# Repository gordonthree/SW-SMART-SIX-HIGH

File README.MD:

# Smart Six-way High Side Switch Node
Compact power management board intended to control six high-side DC loads. The node provides current monitoring of each load, and the board total. Temperature and supply voltage are also monitored. This node works with other CAN-CTL modules using the robust CAN bus interface.

<IMG src="https://github.com/gordonthree/SW-SMART-SIX-HIGH/blob/main/SW-SMART-SIX-HIGH.png?raw=true" width=480>

* STM32G071 microcontroller with 64 pins and 256k flash
* Six Infineon BTS7002 Profet Smart Switches for high side loads; firmware limited to 15 amps each
* Allegro ACS712 on board to monitor total board current; firmware limited to 30 amps
* Microchip MCP2562 isolated CAN bus transceiver
* Microchip MCP9701 board mount temperature sensor
* Voltage divider to monitor supply voltage
* Each switch provides current monitoring and diagnostics
* Screw terminal block for CAN bus connection
* Screw terminal block for power-out, up to 12 AWG
* Heavy duty screw terminals for power in, up to 6 AWG cable
* Headers for SWD programming and USART2 serial port

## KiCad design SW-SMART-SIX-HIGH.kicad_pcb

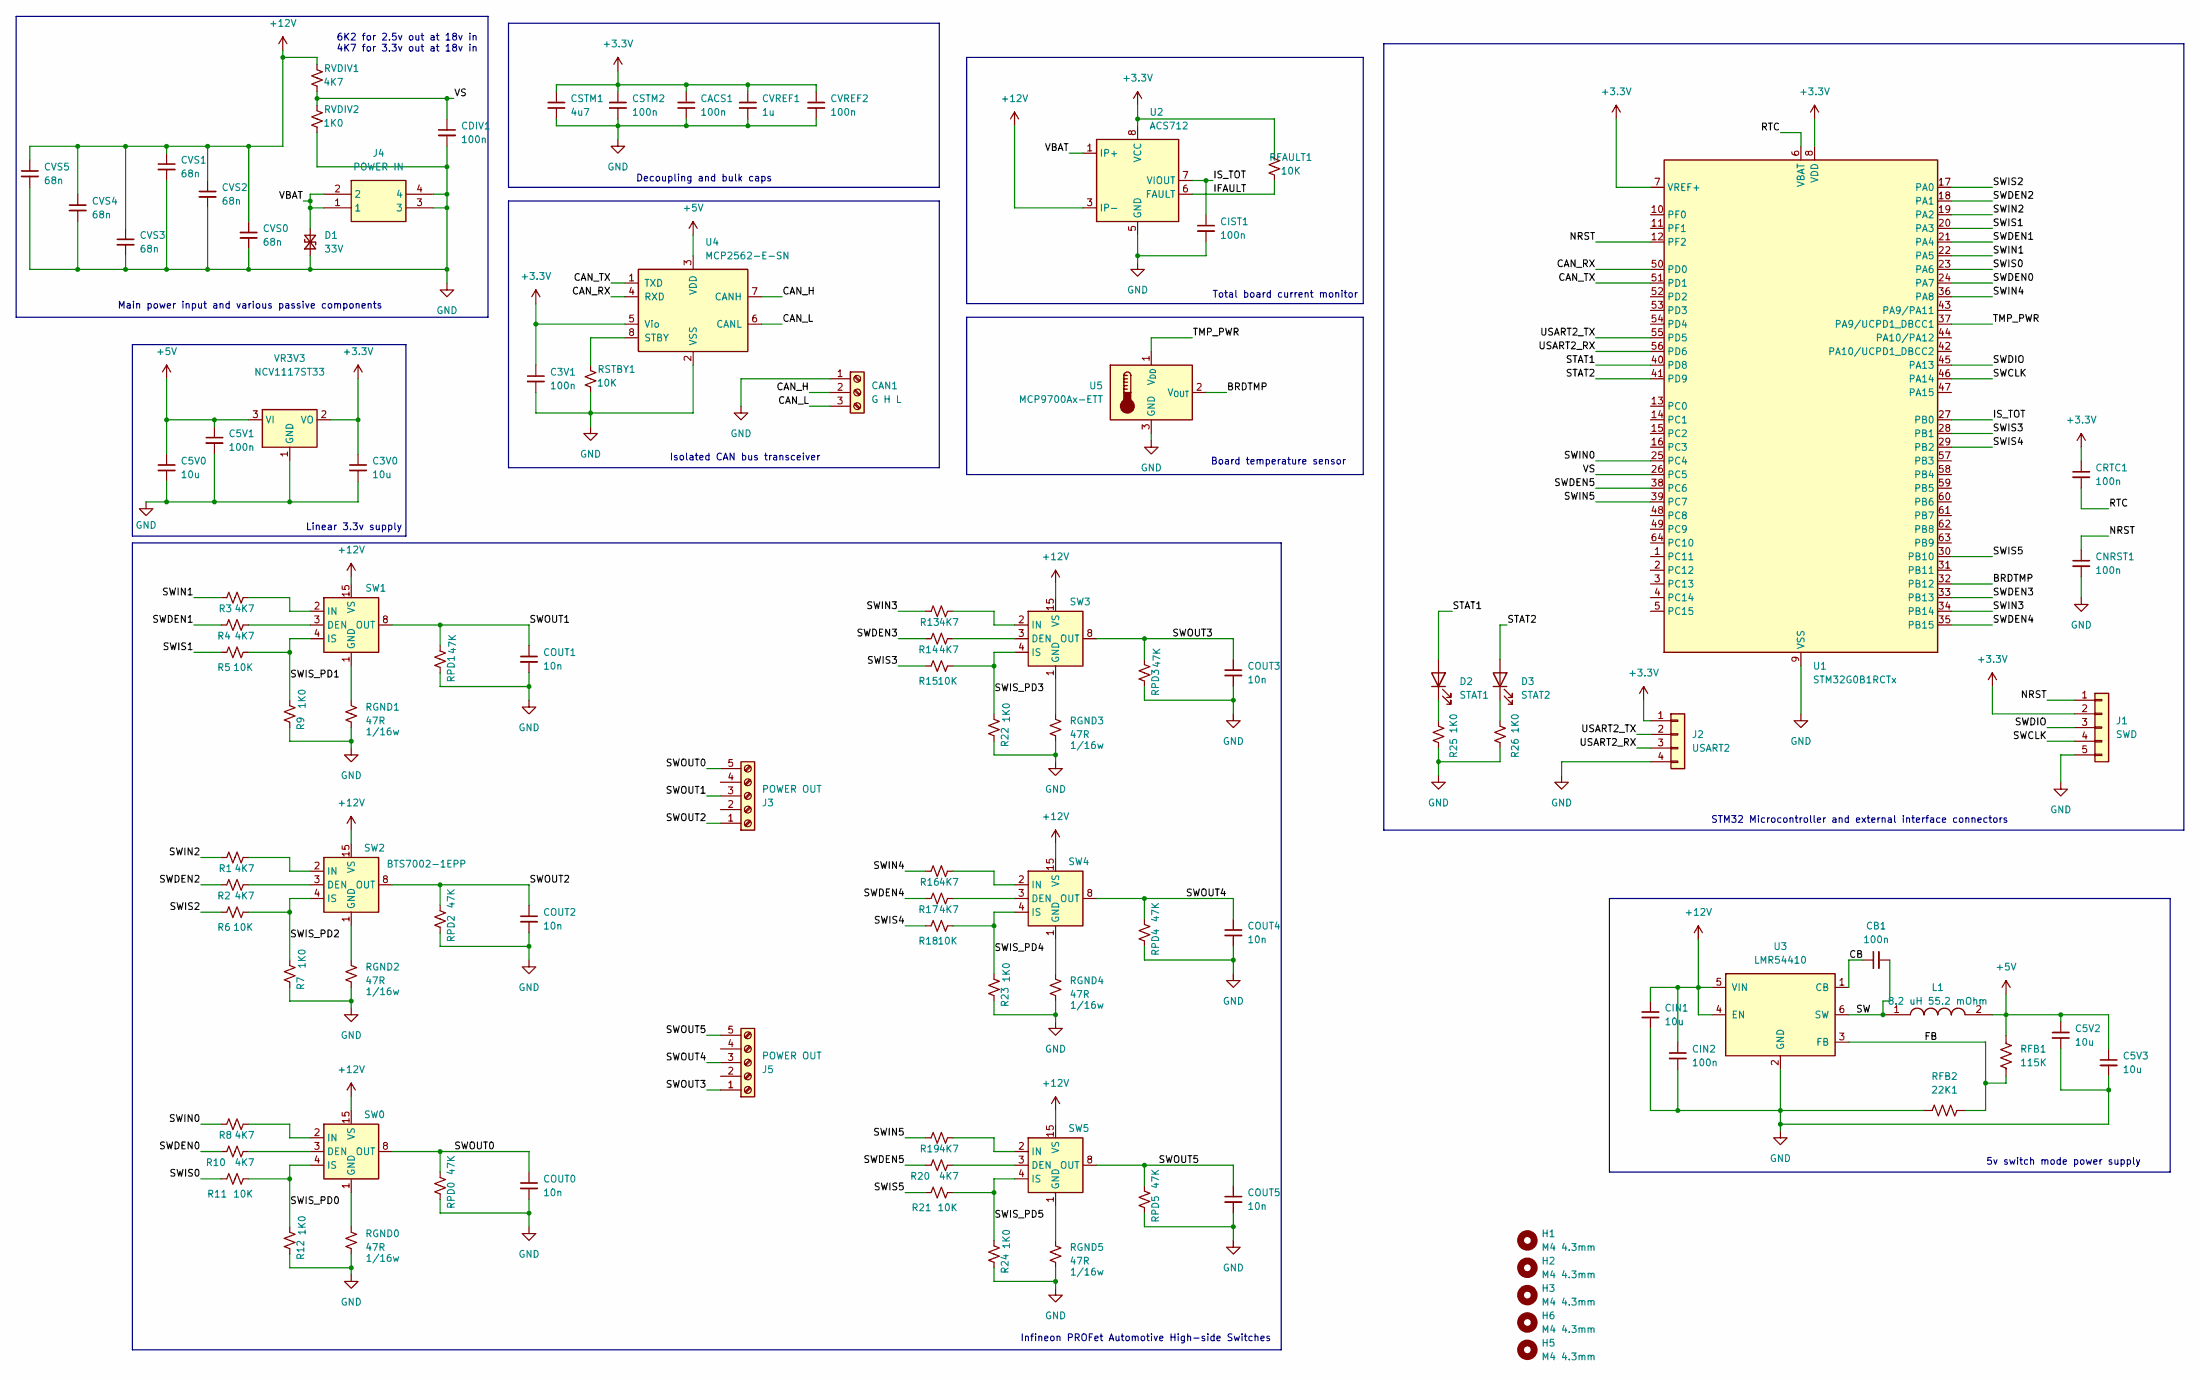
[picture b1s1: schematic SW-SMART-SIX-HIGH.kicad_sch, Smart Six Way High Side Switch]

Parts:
C3V0, C5V0, C5V2, C5V3: 10u; C_0805_2012Metric_Pad1.18x1.45mm_HandSolder
C3V1, C5V1: 100n; C_0603_1608Metric_Pad1.08x0.95mm_HandSolder
CACS1: 100n; C_0603_1608Metric_Pad1.08x0.95mm_HandSolder
CAN1: G H L; TerminalBlock_Phoenix_MPT-0,5-3-2.54_1x03_P2.54mm_Horizontal
CB1: 100n; C_0603_1608Metric_Pad1.08x0.95mm_HandSolder
CDIV1: 100n; C_0603_1608Metric_Pad1.08x0.95mm_HandSolder
CIN1: 10u; C_1210_3225Metric_Pad1.33x2.70mm_HandSolder
CIN2: 100n; C_0603_1608Metric_Pad1.08x0.95mm_HandSolder
CIST1: 100n; C_0603_1608Metric_Pad1.08x0.95mm_HandSolder
CNRST1: 100n; C_0603_1608Metric_Pad1.08x0.95mm_HandSolder
COUT0, COUT1, COUT2, COUT3, COUT4, COUT5: 10n; C_0603_1608Metric_Pad1.08x0.95mm_HandSolder
CRTC1: 100n; C_0603_1608Metric_Pad1.08x0.95mm_HandSolder
CSTM1: 4u7; C_0805_2012Metric_Pad1.18x1.45mm_HandSolder
CSTM2: 100n; C_0603_1608Metric_Pad1.08x0.95mm_HandSolder
CVREF1: 1u; C_0805_2012Metric_Pad1.18x1.45mm_HandSolder
CVREF2: 100n; C_0603_1608Metric_Pad1.08x0.95mm_HandSolder
CVS0, CVS1, CVS2, CVS3, CVS4, CVS5: 68n; C_0603_1608Metric_Pad1.08x0.95mm_HandSolder
D1: 33V; D_SMA_Handsoldering
D2: STAT1; LED_0805_2012Metric_Pad1.15x1.40mm_HandSolder
D3: STAT2; LED_0805_2012Metric_Pad1.15x1.40mm_HandSolder
H1, H2, H3, H5, H6: M4 4.3mm; MountingHole_4.3mm_M4
J1: SWD; PinHeader_1x05_P2.54mm_Vertical
J2: USART2; PinHeader_1x04_P2.54mm_Vertical
J3, J5: POWER OUT; TerminalBlock_Phoenix_MKDS-3-5-5.08_1x05_P5.08mm_Horizontal
J4: POWER IN; VP0265840000G; Mouser Part Number 649-VP02658400J0G
L1: 8.2 uH 55.2 mOhm; SRP5030HMT-8R2M; Mouser Part Number SRP5030HMT-8R2M
R1, R2, R3, R4, R8, R10, R13, R14, R16, R17, R19, R20: 4K7; R_0603_1608Metric_Pad0.98x0.95mm_HandSolder
R5, R6, R11, R15, R18, R21: 10K; R_0603_1608Metric_Pad0.98x0.95mm_HandSolder
R7, R9, R12, R22, R23, R24, R25, R26: 1K0; R_0603_1608Metric_Pad0.98x0.95mm_HandSolder
RFAULT1: 10K; R_0603_1608Metric_Pad0.98x0.95mm_HandSolder
RFB1: 115K; R_0603_1608Metric_Pad0.98x0.95mm_HandSolder
RFB2: 22K1; R_0603_1608Metric_Pad0.98x0.95mm_HandSolder
RGND0, RGND1, RGND2, RGND3, RGND4, RGND5: 47R; R_0603_1608Metric_Pad0.98x0.95mm_HandSolder
RPD0, RPD1, RPD2, RPD3, RPD4, RPD5: 47K; R_0603_1608Metric_Pad0.98x0.95mm_HandSolder
RSTBY1: 10K; R_0603_1608Metric_Pad0.98x0.95mm_HandSolder
RVDIV1: 4K7; R_0603_1608Metric_Pad0.98x0.95mm_HandSolder
RVDIV2: 1K0; R_0603_1608Metric_Pad0.98x0.95mm_HandSolder
SW0, SW1, SW2, SW3, SW4, SW5: BTS7002-1EPP; SOP65P600X115-15N
U1: STM32G0B1RCTx; LQFP-64_10x10mm_P0.5mm
U2: ACS712; SOIC-8_3.9x4.9mm_P1.27mm; Part Number ACS71240LLCBTR-050B3
U3: LMR54410; SOT-23-6
U4: MCP2562-E-SN; SOIC-8_3.9x4.9mm_P1.27mm
U5: MCP9700Ax-ETT; SOT-23
VR3V3: NCV1117ST33; SOT-223-3_TabPin2

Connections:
+3.3V: C3V0.1, C3V1.1, CACS1.1, CRTC1.1, CSTM1.1, CSTM2.1, CVREF1.1, CVREF2.1, J1.2, J2.1, RFAULT1.2, U1.7 (VREF+), U1.8 (VDD), U2.8 (VCC), U4.5 (Vio), VR3V3.2 (VO); also elsewhere on the board
+5V: C5V0.1, C5V1.1, C5V2.1, C5V3.1, L1.2, RFB1.1, U4.3 (VDD), VR3V3.3 (VI)
+12V: CIN1.1, CIN2.1, CVS0.1, CVS1.1, CVS2.1, CVS3.1, CVS4.1, CVS5.1, RVDIV1.2, SW0.15 (VS), SW1.15 (VS), SW2.15 (VS), SW3.15 (VS), SW4.15 (VS), SW5.15 (VS), U2.3 (IP-), U2.4 (IP-), U3.4 (EN), U3.5 (VIN)
/BRDTMP: U1.32 (PB12), U5.2 (V_{OUT})
/CAN_H: CAN1.2, U4.7 (CANH)
/CAN_L: CAN1.3, U4.6 (CANL)
/CAN_RX: U1.50 (PD0), U4.4 (RXD)
/CAN_TX: U1.51 (PD1), U4.1 (TXD)
/CB: CB1.1, U3.1 (CB)
/FB: RFB1.2, RFB2.2, U3.3 (FB)
/IFAULT: RFAULT1.1, U2.6 (FAULT)
/IS_TOT: CIST1.1, U1.27 (PB0), U2.7 (VIOUT)
/NRST: CNRST1.1, J1.1, U1.12 (PF2)
/OSC: U1.10 (PF0); also elsewhere on the board
/RTC: CRTC1.2, U1.6 (VBAT)
/STAT1: D2.2 (A), U1.40 (PD8)
/STAT2: D3.2 (A), U1.41 (PD9)
/SW: CB1.2, L1.1, U3.6 (SW)
/SWCLK: J1.4, U1.46 (PA14)
/SWDEN0: R10.1, U1.24 (PA7)
/SWDEN1: R4.1, U1.21 (PA4)
/SWDEN2: R2.1, U1.18 (PA1)
/SWDEN3: R14.1, U1.33 (PB13)
/SWDEN4: R17.1, U1.35 (PB15)
/SWDEN5: R20.1, U1.38 (PC6)
/SWDIO: J1.3, U1.45 (PA13)
/SWIN0: R8.1, U1.25 (PC4)
/SWIN1: R3.1, U1.22 (PA5)
/SWIN2: R1.1, U1.19 (PA2)
/SWIN3: R13.1, U1.34 (PB14)
/SWIN4: R16.1, U1.36 (PA8)
/SWIN5: R19.1, U1.39 (PC7)
/SWIS0: R11.1, U1.23 (PA6)
/SWIS1: R5.1, U1.20 (PA3)
/SWIS2: R6.1, U1.17 (PA0)
/SWIS3: R15.1, U1.28 (PB1)
/SWIS4: R18.1, U1.29 (PB2)
/SWIS5: R21.1, U1.30 (PB10)
/SWIS_PD0: R11.2, R12.2, SW0.4 (IS)
/SWIS_PD1: R5.2, R9.2, SW1.4 (IS)
/SWIS_PD2: R6.2, R7.2, SW2.4 (IS)
/SWIS_PD3: R15.2, R22.2, SW3.4 (IS)
/SWIS_PD4: R18.2, R23.2, SW4.4 (IS)
/SWIS_PD5: R21.2, R24.2, SW5.4 (IS)
/SWOUT0: COUT0.1, J3.5, RPD0.2, SW0.8 (OUT), SW0.9 (OUT), SW0.10 (OUT), SW0.12 (OUT), SW0.13 (OUT), SW0.14 (OUT)
/SWOUT1: COUT1.1, J3.3, RPD1.2, SW1.8 (OUT), SW1.9 (OUT), SW1.10 (OUT), SW1.12 (OUT), SW1.13 (OUT), SW1.14 (OUT)
/SWOUT2: COUT2.1, J3.1, RPD2.2, SW2.8 (OUT), SW2.9 (OUT), SW2.10 (OUT), SW2.12 (OUT), SW2.13 (OUT), SW2.14 (OUT)
/SWOUT3: COUT3.1, J5.1, RPD3.2, SW3.8 (OUT), SW3.9 (OUT), SW3.10 (OUT), SW3.12 (OUT), SW3.13 (OUT), SW3.14 (OUT)
/SWOUT4: COUT4.1, J5.3, RPD4.2, SW4.8 (OUT), SW4.9 (OUT), SW4.10 (OUT), SW4.12 (OUT), SW4.13 (OUT), SW4.14 (OUT)
/SWOUT5: COUT5.1, J5.5, RPD5.2, SW5.8 (OUT), SW5.9 (OUT), SW5.10 (OUT), SW5.12 (OUT), SW5.13 (OUT), SW5.14 (OUT)
/TMP_PWR: U1.37 (PA9/UCPD1_DBCC1), U5.1 (V_{DD})
/USART2_RX: J2.3, U1.56 (PD6)
/USART2_TX: J2.2, U1.55 (PD5)
/VBAT: D1.2 (A2), J4.1, J4.2, U2.1 (IP+), U2.2 (IP+)
/VS: CDIV1.1, RVDIV1.1, RVDIV2.2, U1.26 (PC5)
GND: C3V0.2, C3V1.2, C5V0.2, C5V1.2, C5V2.2, C5V3.2, CACS1.2, CAN1.1, CDIV1.2, CIN1.2, CIN2.2, CIST1.2, CNRST1.2, COUT0.2, COUT1.2, COUT2.2, COUT3.2, COUT4.2, COUT5.2, CSTM1.2, CSTM2.2, CVREF1.2, CVREF2.2, CVS0.2, CVS1.2, CVS2.2, CVS3.2, CVS4.2, CVS5.2, D1.1 (A1), J1.5, J2.4, J4.3, J4.4, R7.1, R9.1, R12.1, R22.1, R23.1, R24.1, R25.1, R26.1, RFB2.1, RGND0.2, RGND1.2, RGND2.2, RGND3.2, RGND4.2, RGND5.2, RPD0.1, RPD1.1, RPD2.1, RPD3.1, RPD4.1, RPD5.1, RSTBY1.1, RVDIV2.1, U1.9 (VSS), U2.5 (GND), U3.2 (GND), U4.2 (VSS), U5.3 (GND), VR3V3.1 (GND); also elsewhere on the board
unnamed: D2.1 (K), R25.2
unnamed: D3.1 (K), R26.2
unnamed: R10.2, SW0.3 (DEN)
unnamed: RGND0.1, SW0.1 (GND)
unnamed: R8.2, SW0.2 (IN)
unnamed: R4.2, SW1.3 (DEN)
unnamed: RGND1.1, SW1.1 (GND)
unnamed: R3.2, SW1.2 (IN)
unnamed: R2.2, SW2.3 (DEN)
unnamed: RGND2.1, SW2.1 (GND)
unnamed: R1.2, SW2.2 (IN)
unnamed: R14.2, SW3.3 (DEN)
unnamed: RGND3.1, SW3.1 (GND)
unnamed: R13.2, SW3.2 (IN)
unnamed: R17.2, SW4.3 (DEN)
unnamed: RGND4.1, SW4.1 (GND)
unnamed: R16.2, SW4.2 (IN)
unnamed: R20.2, SW5.3 (DEN)
unnamed: RGND5.1, SW5.1 (GND)
unnamed: R19.2, SW5.2 (IN)
unnamed: RSTBY1.2, U4.8 (STBY)

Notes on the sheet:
Isolated CAN bus transceiver
6K2 for 2.5v out at 18v in 4K7 for 3.3v out at 18v in
Total board current monitor
Linear 3.3v supply
Main power input and various passive components
STM32 Microcontroller and external interface connectors
Infineon PROFet Automotive High-side Switches
Decoupling and bulk caps
5v switch mode power supply
Board temperature sensor

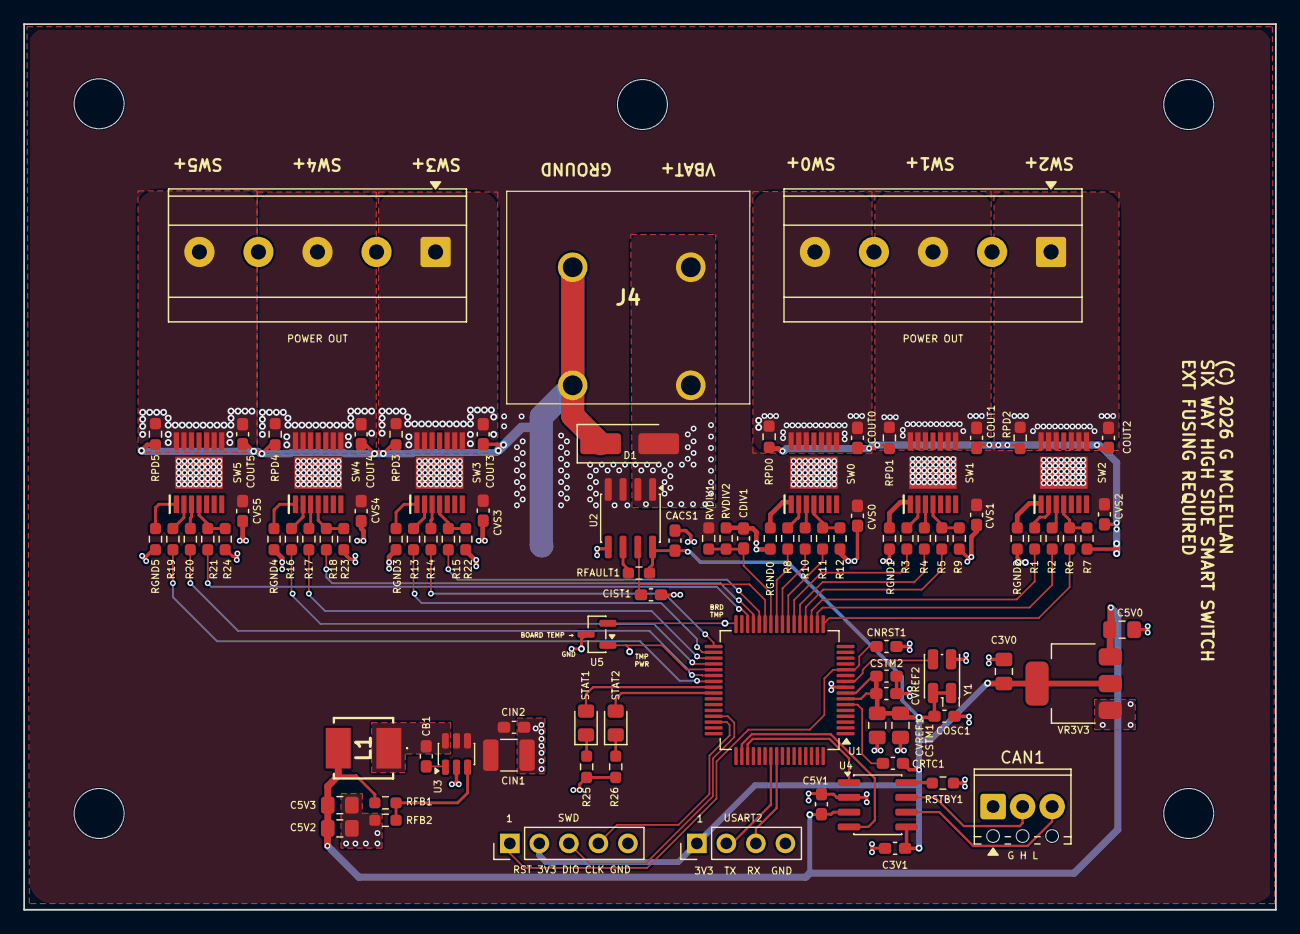
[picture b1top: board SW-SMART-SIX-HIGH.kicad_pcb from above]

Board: 2 copper layers, 107.7 x 76.2 mm, 103 parts (0 on the bottom side), 77 nets.

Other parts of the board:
COSC1: 100n; C_0603_1608Metric_Pad1.08x0.95mm_HandSolder
Y1: 8MHz; Oscillator_SMD_EuroQuartz_XO32-4Pin_3.2x2.5mm_RotB_HandSold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

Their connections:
+3.3V: COSC1.1, Y1.1 (~ST), Y1.4 (VCC); also elsewhere on the board
/OSC: Y1.3 (OUT); also elsewhere on the board
GND: COSC1.2, Y1.2 (GND); also elsewhere on the board

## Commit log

2026-01-21 lots of work to do!
2026-01-21 added ACS712 to monitor total board current
2026-01-21 layout starting to take shape
2026-01-21 update feature list
2026-01-22 swapped to a 48pin uC
2026-01-22 layout work continues
2026-01-22 lots of work to do still
2026-01-22 making progress on layout and routing
2026-01-22 I think I'm done adding components
2026-01-22 update to the 64pin micro
2026-01-22 update uC details
2026-01-22 great progress with routing so far
2026-01-22 signals routed, next is power
2026-01-22 updated rendering
2026-01-22 everything is routed, drc passed
2026-01-22 Schematic cleanup and documentation
2026-01-22 clarify the readme
2026-01-22 rename swlink to swd
2026-01-22 fine tune a few things
2026-01-22 fix a few issues that cropped up
2026-01-22 update rendering
2026-01-22 update embedded image url
2026-01-23 added dedicated board temperature sensor
2026-01-23 added dedicated board temp sensor and some silkscreen tweaks
2026-01-23 added board temp sensor
2026-01-23 support files
2026-01-25 remove unneeded files
2026-01-25 changed can connector wiring and footprint size
2026-01-25 updated can bus connector footprint
2026-01-25 updated embedded image url
2026-01-25 reformat readme, add brief description paragraph
2026-01-25 move the embedded image
2026-01-27 added recommended mcu vref capacitors
2026-01-27 adjusted grounding and copper pour dimensions
2026-02-02 added crystal osc
2026-02-02 updated rendering after adding XO
2026-02-04 outdated schematic pdf

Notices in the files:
SW-SMART-SIX-HIGH.kicad_pcb:
(C) 2026 G MCLELLAN
